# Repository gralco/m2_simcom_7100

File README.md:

# m2_simcom_7100

SIMCom 7100 on a M.2 card.

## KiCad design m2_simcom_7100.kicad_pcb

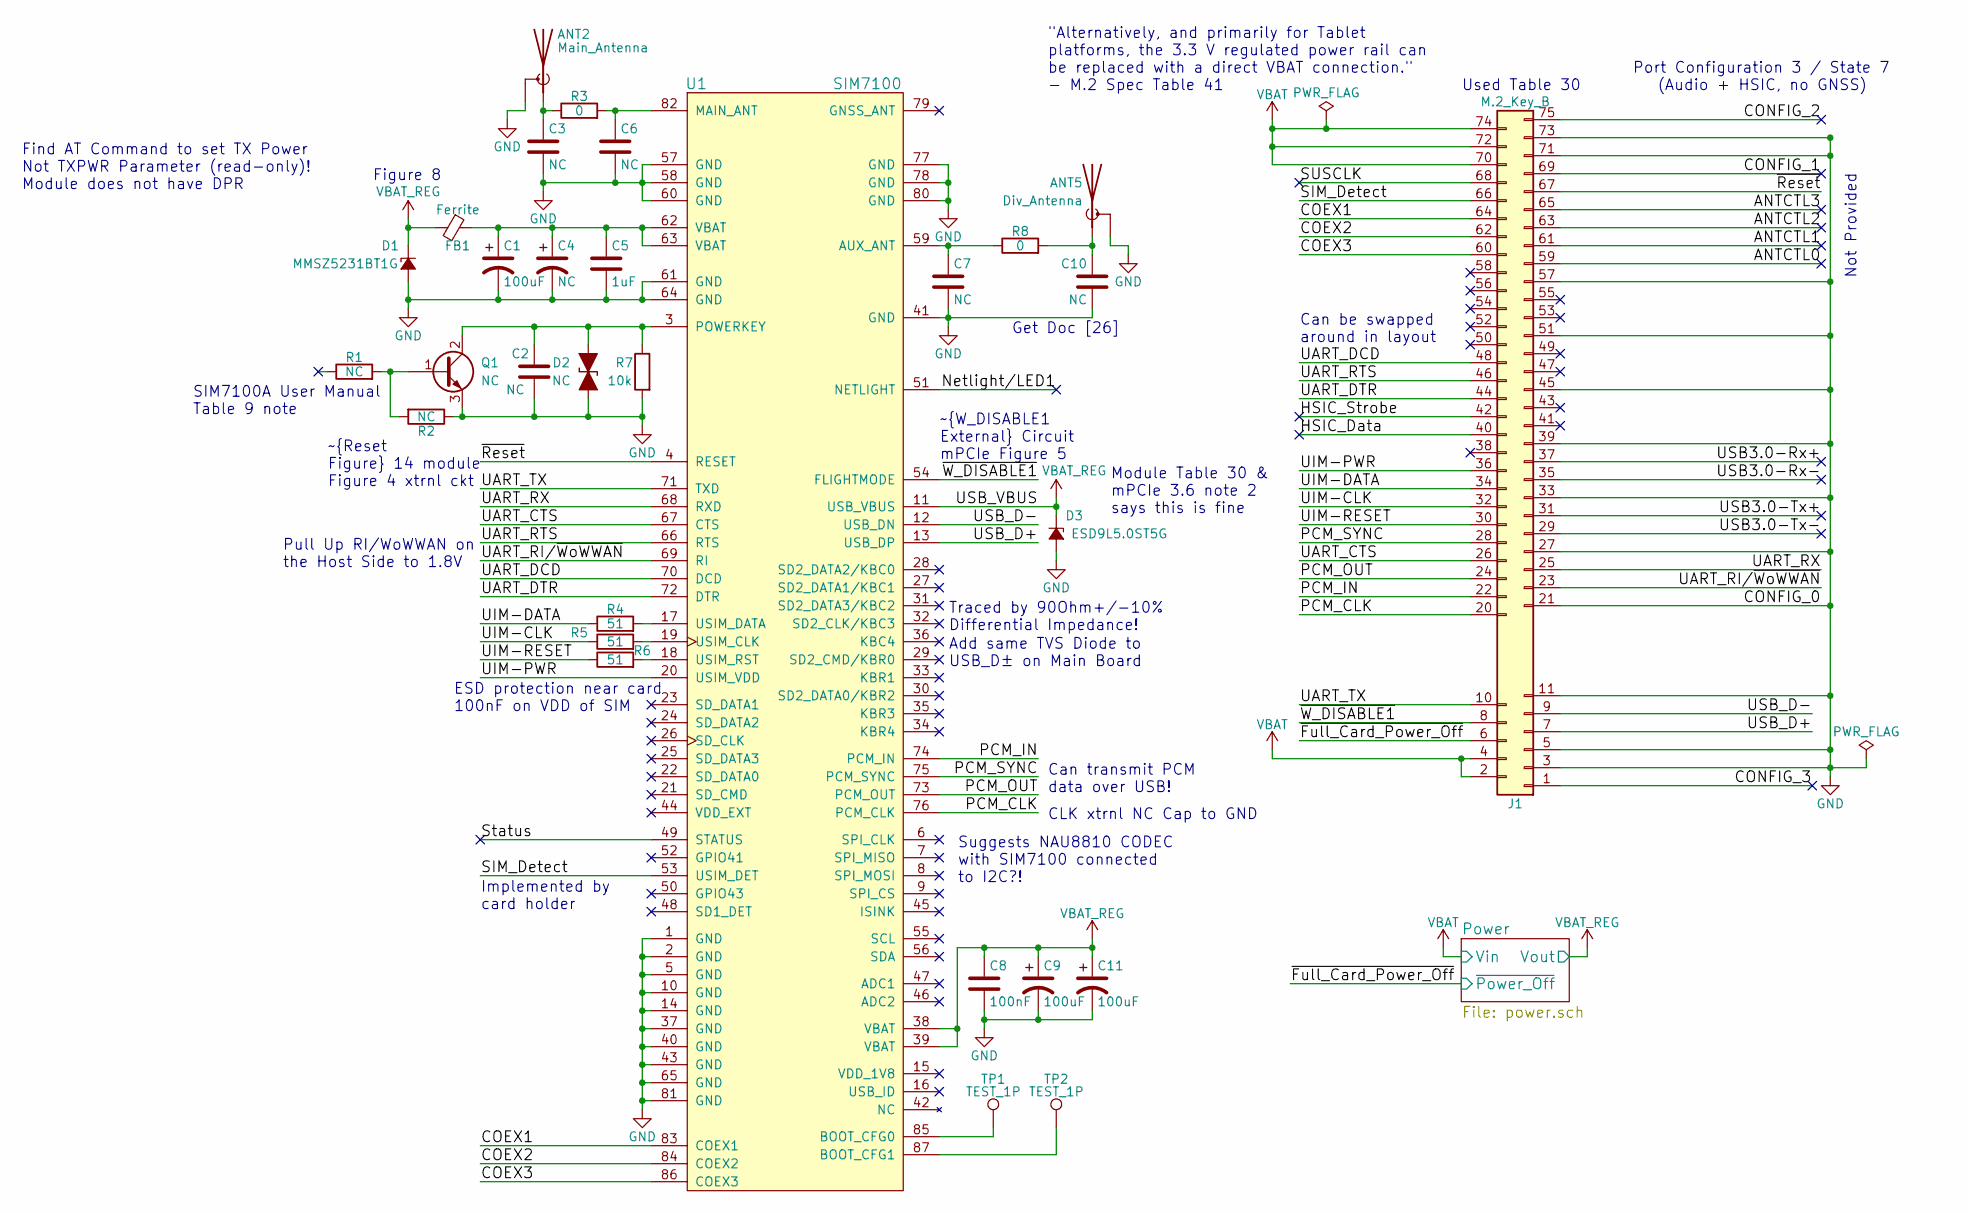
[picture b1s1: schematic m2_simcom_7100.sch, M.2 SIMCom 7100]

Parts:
ANT2: Main_Antenna; MHF4_20449-001E
ANT5: Div_Antenna; MHF4_20449-001E
C1, C9, C11: 100uF; CP_Tantalum_Case-B_EIA-3528-21_Reflow
C2, C3, C6, C7, C10: NC; C_0603
C4: NC; CP_Tantalum_Case-B_EIA-3528-21_Reflow
C5: 1uF; C_0603
C8: 100nF; C_0603
D1: MMSZ5231BT1G; D_SOD-123
D2: NC; D_0402
D3: ESD9L5.0ST5G; D_SOD-923
FB1: Ferrite; L_0603
J1: M.2_Key_B; M.2_Key_B_Gold_Fingers
Q1: NC; SOT-23
R1, R2: NC; R_0603
R3, R8: 0; R_0603
R4, R5, R6: 51; R_0603
R7: 10k; R_0603
TP1, TP2: TEST_1P; Measurement_Point_Round-SMD-Pad_Small
U1: SIM7100; SIMCom_7100

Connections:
/ANTCTL0: J1.59
/ANTCTL1: J1.61
/ANTCTL2: J1.63
/ANTCTL3: J1.65
/COEX1: J1.64, U1.83 (COEX1)
/COEX2: J1.62, U1.84 (COEX2)
/COEX3: J1.60, U1.86 (COEX3)
/CONFIG_1: J1.69
/CONFIG_2: J1.75
/CONFIG_3: J1.1
/HSIC_Data: J1.40
/HSIC_Strobe: J1.42
/Netlight/LED1: U1.51 (NETLIGHT)
/PCM_CLK: J1.20, U1.76 (PCM_CLK)
/PCM_IN: J1.22, U1.74 (PCM_IN)
/PCM_OUT: J1.24, U1.73 (PCM_OUT)
/PCM_SYNC: J1.28, U1.75 (PCM_SYNC)
/SIM_Detect: J1.66, U1.53 (USIM_DET)
/SUSCLK: J1.68
/Status: U1.49 (STATUS)
/UART_CTS: J1.26, U1.67 (CTS)
/UART_DCD: J1.48, U1.70 (DCD)
/UART_DTR: J1.44, U1.72 (DTR)
/UART_RI/~WoWWAN: J1.23, U1.69 (RI)
/UART_RTS: J1.46, U1.66 (RTS)
/UART_RX: J1.25, U1.68 (RXD)
/UART_TX: J1.10, U1.71 (TXD)
/UIM-CLK: J1.32, R5.1
/UIM-DATA: J1.34, R4.1
/UIM-PWR: J1.36, U1.20 (USIM_VDD)
/UIM-RESET: J1.30, R6.1
/USB3.0-Rx+: J1.37
/USB3.0-Rx-: J1.35
/USB3.0-Tx+: J1.31
/USB3.0-Tx-: J1.29
/USB_D+: J1.7, U1.13 (USB_DP)
/USB_D-: J1.9, U1.12 (USB_DN)
/~Full_Card_Power_Off: J1.6; also elsewhere on the board
/~Reset: J1.67, U1.4 (RESET)
/~W_DISABLE1: J1.8, U1.54 (FLIGHTMODE)
GND: ANT2.2 (Shield), ANT5.2 (Shield), C1.2, C2.2, C3.2, C4.2, C5.2, C6.2, C7.2, C8.2, C9.2, C10.2, C11.2, D1.2 (A), D2.2 (A2), D3.2 (A), J1.3, J1.5, J1.11, J1.21, J1.27, J1.33, J1.39, J1.45, J1.51, J1.57, J1.71, J1.73, Q1.3 (E), R2.1, R7.2, U1.1 (GND), U1.2 (GND), U1.5 (GND), U1.10 (GND), U1.14 (GND), U1.37 (GND), U1.40 (GND), U1.41 (GND), U1.43 (GND), U1.57 (GND), U1.58 (GND), U1.60 (GND), U1.61 (GND), U1.64 (GND), U1.65 (GND), U1.77 (GND), U1.78 (GND), U1.80 (GND), U1.81 (GND); also elsewhere on the board
unnamed: ANT2.1 (A), C3.1, R3.1
unnamed: ANT5.1 (A), C10.1, R8.2
unnamed: C1.1, C4.1, C5.1, FB1.1, U1.62 (VBAT), U1.63 (VBAT)
unnamed: C2.1, D2.1 (A1), Q1.2 (C), R7.1, U1.3 (POWERKEY)
unnamed: C6.1, R3.2, U1.82 (MAIN_ANT)
unnamed: C7.1, R8.1, U1.59 (AUX_ANT)
unnamed: Q1.1 (B), R1.2, R2.2
unnamed: R4.2, U1.17 (USIM_DATA)
unnamed: R5.2, U1.19 (USIM_CLK)
unnamed: R6.2, U1.18 (USIM_RST)
unnamed: TP1.1, U1.85 (BOOT_CFG0)
unnamed: TP2.1, U1.87 (BOOT_CFG1)
VBAT: J1.2, J1.4, J1.70, J1.72, J1.74; also elsewhere on the board
VBAT_REG: C8.1, C9.1, C11.1, D1.1 (K), D3.1 (K), FB1.2, U1.11 (USB_VBUS), U1.38 (VBAT), U1.39 (VBAT); also elsewhere on the board

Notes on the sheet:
Used Table 30
Port Configuration 3 / State 7 (Audio + HSIC, no GNSS)
ESD protection near card 100nF on VDD of SIM
Not Provided
Traced by 90Ohm+/-10% Differential Impedance!
Find AT Command to set TX Power Not TXPWR Parameter (read-only)! Module does not have DPR
Can be swapped around in layout
Pull Up RI/WoWWAN on the Host Side to 1.8V
Add same TVS Diode to USB_D± on Main Board
Implemented by card holder
~W_DISABLE1 External Circuit mPCIe Figure 5
Can transmit PCM data over USB!
Suggests NAU8810 CODEC with SIM7100 connected to I2C?!
CLK xtrnl NC Cap to GND
Module Table 30 & mPCIe 3.6 note 2 says this is fine
~Reset Figure 14 module Figure 4 xtrnl ckt
Get Doc [26]
SIM7100A User Manual Table 9 note
"Alternatively, and primarily for Tablet platforms, the 3.3 V regulated power rail can be replaced with a direct VBAT connection." - M.2 Spec Table 41
Figure 8

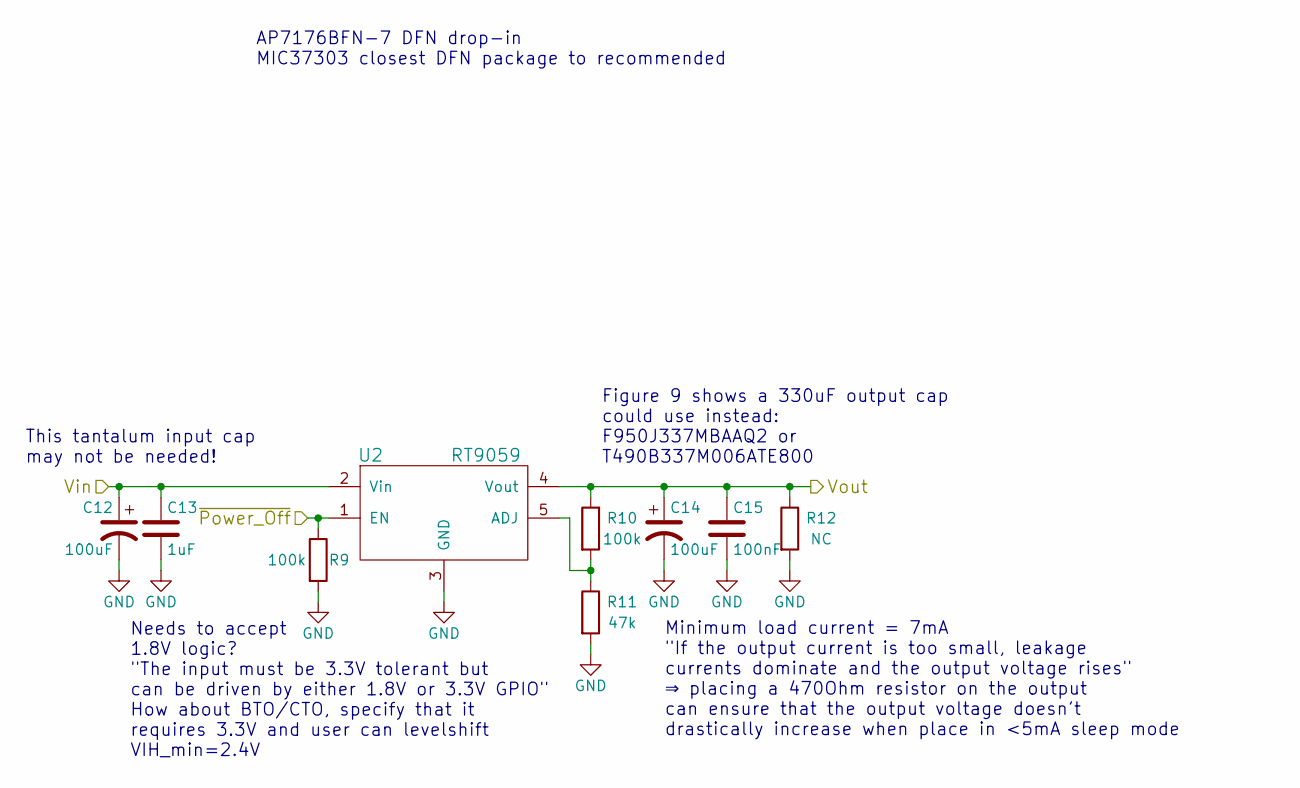
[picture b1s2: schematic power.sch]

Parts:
C12, C14: 100uF; CP_Tantalum_Case-B_EIA-3528-21_Reflow
C13: 1uF; C_0603
C15: 100nF; C_0603
R9, R10: 100k; R_0603
R11: 47k; R_0603
R12: NC; R_0603
U2: RT9059

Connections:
/~Full_Card_Power_Off: R9.1, U2.1 (EN); also elsewhere on the board
GND: C12.2, C13.2, C14.2, C15.2, R9.2, R11.2, R12.2, U2.3 (GND), U2.6 (GND); also elsewhere on the board
unnamed: R10.2, R11.1, U2.5 (ADJ)
VBAT: C12.1, C13.1, U2.2 (Vin); also elsewhere on the board
VBAT_REG: C14.1, C15.1, R10.1, R12.1, U2.4 (Vout); also elsewhere on the board

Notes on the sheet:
Needs to accept 1.8V logic? "The input must be 3.3V tolerant but can be driven by either 1.8V or 3.3V GPIO" How about BTO/CTO, specify that it requires 3.3V and user can levelshift VIH_min=2.4V
Minimum load current = 7mA "If the output current is too small, leakage currents dominate and the output voltage rises" ⇒ placing a 470Ohm resistor on the output can ensure that the output voltage doesn't drastically increase when place in <5mA sleep mode
Figure 9 shows a 330uF output cap could use instead: F950J337MBAAQ2 or T490B337M006ATE800
This tantalum input cap may not be needed!
AP7176BFN-7 DFN drop-in MIC37303 closest DFN package to recommended

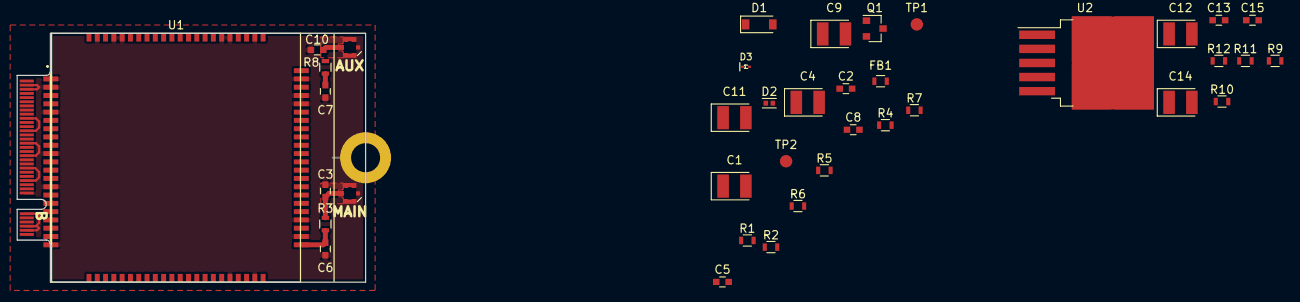
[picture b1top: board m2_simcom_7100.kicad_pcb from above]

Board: 2 copper layers, 42.0 x 30.0 mm, 39 parts (0 on the bottom side), 40 nets.

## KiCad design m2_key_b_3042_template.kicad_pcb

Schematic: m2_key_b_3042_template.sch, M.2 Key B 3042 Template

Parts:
ANT1, ANT2, ANT4: Conn_Coaxial; MHF4_20449-001E
J1: M.2_Key_B; M.2_Key_B_Gold_Fingers

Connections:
+3V3: J1.2, J1.4, J1.70, J1.72, J1.74
/ANTCTL0: J1.59
/ANTCTL1: J1.61
/ANTCTL2: J1.63
/ANTCTL3: J1.65
/AUX: ANT1.1
/COEX1: J1.64
/COEX2: J1.62
/COEX3: J1.60
/CONFIG_0: J1.21
/CONFIG_1: J1.69
/CONFIG_2: J1.75
/CONFIG_3: J1.1
/DEVSLP: J1.38
/GPIO_0: J1.40
/GPIO_1: J1.42
/GPIO_2: J1.44
/GPIO_3: J1.46
/GPIO_4: J1.48
/GPIO_5: J1.20
/GPIO_6: J1.22
/GPIO_7: J1.24
/GPIO_8: J1.28
/GPIO_9/DAS/~DSS: J1.10
/GPIO_10: J1.26
/GPIO_11: J1.23
/GPIO_12: J1.25
/GPS: ANT2.1
/MAIN: ANT4.1
/PERn0/SATA-B+: J1.41
/PERn1/USB3.0-Rx-/SSIC-RxN: J1.29
/PERp0/SATA-B-: J1.43
/PERp1/USB3.0-Rx+/SSIC-RxP: J1.31
/PETn0/SATA-A-: J1.47
/PETn1/USB3.0-Tx-/SSIC-TxN: J1.35
/PETp0/SATA-A+: J1.49
/PETp1/USB3.0-Tx+/SSIC-TxP: J1.37
/REFCLKN: J1.53
/REFCLKP: J1.55
/SIM_Detect: J1.66
/SUSCLK: J1.68
/UIM-CLK: J1.32
/UIM-DATA: J1.34
/UIM-PWR: J1.36
/UIM-RESET: J1.30
/USB_D+: J1.7
/USB_D-: J1.9
/~CLKREQ: J1.52
/~Full_Card_Power_Off: J1.6
/~PERST: J1.50
/~PEWake: J1.54
/~Reset: J1.67
/~W_DISABLE1: J1.8
GND: ANT1.2, ANT2.2, ANT4.2, J1.3, J1.5, J1.11, J1.27, J1.33, J1.39, J1.45, J1.51, J1.57, J1.71, J1.73

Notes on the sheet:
???
(Used Table 48) CHECK TABLE 29/30!!!
Unfortunately, it seems most WWAN modules don't explicitly support SSIC This will need to be looked into: "SSIC brings 80% power savings using a MIPI M-PHY and SSIC, as compared to a USB 3.0 PHY"
Huawei MU736 is an example of 3G M.2 card which supports SSIC The i.MX 8M does not explicity state SSIC support
"HSIC supported on WWAN configuration 3"

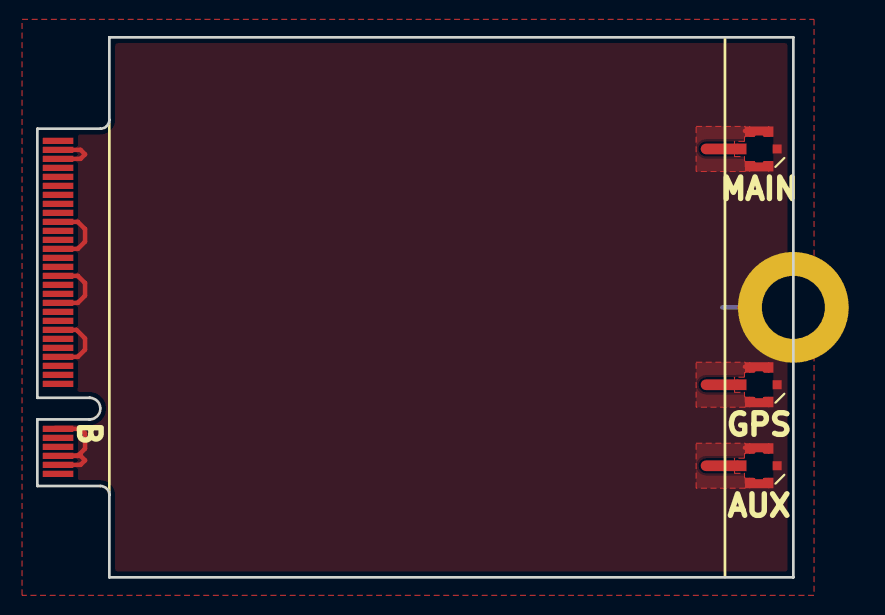
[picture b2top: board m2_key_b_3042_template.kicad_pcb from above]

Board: 2 copper layers, 42.0 x 30.0 mm, 4 parts (0 on the bottom side), 2 nets.

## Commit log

2018-03-13 Add all project files
2018-03-15 Include MHF4 coax connectors for the baseband, diversity, and GNSS antennae
    Improved the soldermask and mounting hole.
    Included silkscreen designating the component area.
    Antennae MHF4 coax connectors show what orientation they need to be placed in (chamfer).
2018-03-15 Plot schematic to PDF and included title block info
2018-03-15 Add MHF4 datasheet to the field values and remove the text reference
2018-03-15 Add coplanar waveguide calculations for the MHF4 antennae tracks
2018-03-16 Include antennae track transmission line impedance calculations which are as close as possible to the expected true value.
    Using the MHF4 recommended 0.6mm track width and 0.12mm space for the 50Ohm CPW.
    Used 4PCB's FR406 relative permitivity and dielectric loss factor values.
    Used slightly less ideal values for the various constants.
2018-03-16 Include copper zones which control the 50Ohm coplanar waveguide for the antennae.
2018-03-16 Fix unconnected ground nets on MHF4 connectors.
    DRC no longer complains about the polygon shaped GND pads of the MHF4 footprints.
2018-03-16 Work around KiCad Bug #1460787 by making ground filled zones located at the CPW for the antennae the same priority level (0).
    Changing any value in thes "encapsulated" filled zones will cause them to disappear!!!
    Currently DRC is not complaining but it may later on with certain edits.
2018-03-16 Include smaller custom 0.508mm diameter 0.254mm drill sized via
2018-03-16 Reduce the area of the no-fill zone keeping the bottom ground pour from getting close to the gold finger connector on either edge of the board.
2018-03-16 Update the outer filled zone parameters to be closer to the default whilst still giving the recommended 0.25mm clearance away from the gold finger connector.
2018-03-16 Add note about signal integrity for routing
2018-03-16 Rename all project related files and references to m2_simcom_7100
2018-03-16 Update the title block to reflect the name change
2018-03-16 Update the footprint library description to reflect the name change
2018-03-16 Update the footprint nickname and library path to reflect the name change too
2018-03-16 Rename the gerber files to reflect the name change
2018-03-16 Add SIMCom 7100 footprint
    Pad dimensions might need to change depending on the orientation placed on the M.2 card.
2018-03-17 Update SIMCom 7100 footprint basaed on what its orientation will be on the M.2 card, added silkscreen to denote pin 1
2018-03-19 add SIM7100 schematic symbol
2018-03-20 Save progress just before replacing pins 10, 23, 25, 26, 44, 46, and 48 with UART pins due to it being Port Configuration 3 / State 7 (no GNSS)
    Pins 10 ~LED1 and 25 DPR (DPR unavailable anyway) being the most practical alternate functions
    Pin 26 was ~W_Disable2 but it was unused anyway, and even if it were it would meant for GNSS anyway (~W_Disable1 takes care of both here)
2018-03-20 Remove GNSS antenna circuit and place notes regarding external circuit
    Add power sheet for the boost converter for Vbat (3.8V) and Vbus (tie to Vbat)
2018-03-20 Add MIC29302 LDO, VBAT will be used instead of 3.3V in order to reduce power consumption.
    When testing this will require a ~3.8V supply at the M.2 connector!
2018-03-21 Selected which bulk capacitors will be used throughout the design, allowing for a small profile with high capacitance and fast transient response time (low ESR/ESL); also created the respective footp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
    Put in a few notes regarding discrepancies between what the SIM7100 documentation suggests for cap values and what the MIC29302 datasheet says. I chose to go wivalues closer to what SIM7100 suggests 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
2018-03-22 Assign all footprints and generate netlist
2018-03-22 Fix footprint associations in netlist which are pointing to the wrong library name
2018-03-22 Swap Main and Div antenna positions
2018-03-22 Import the netlist and associated footprints into the layout
2018-03-23 Swapping out the MIC29302 4.46mm thick TO-263 LDO with the smaller RT9059 WDFN-10L part which can handle the high current transients in a much more suitable package
    The package is also much cheaper!
2018-03-23 Use the RT9059 LDO in the layout instead of the old MIC29302 one
2018-04-12 Add 74AUP1G04 schmitt-triggered inverter to SIM_DET based on the fact that most WWAN M.2 modules expect this to be an active HIGH input
2018-04-13 Make UART interface null modem instead of full modem
    Full modem is unnecessary since the modem can be woken via USB. There's no dedicated DTR, DSR, or DCD lines on the i.MX8M. Generally simpler to implement standard UART (Null Modem).

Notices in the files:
m2_key_b_3042_template.kicad_pcb:
Copyright 2018
GNU GPLv3
